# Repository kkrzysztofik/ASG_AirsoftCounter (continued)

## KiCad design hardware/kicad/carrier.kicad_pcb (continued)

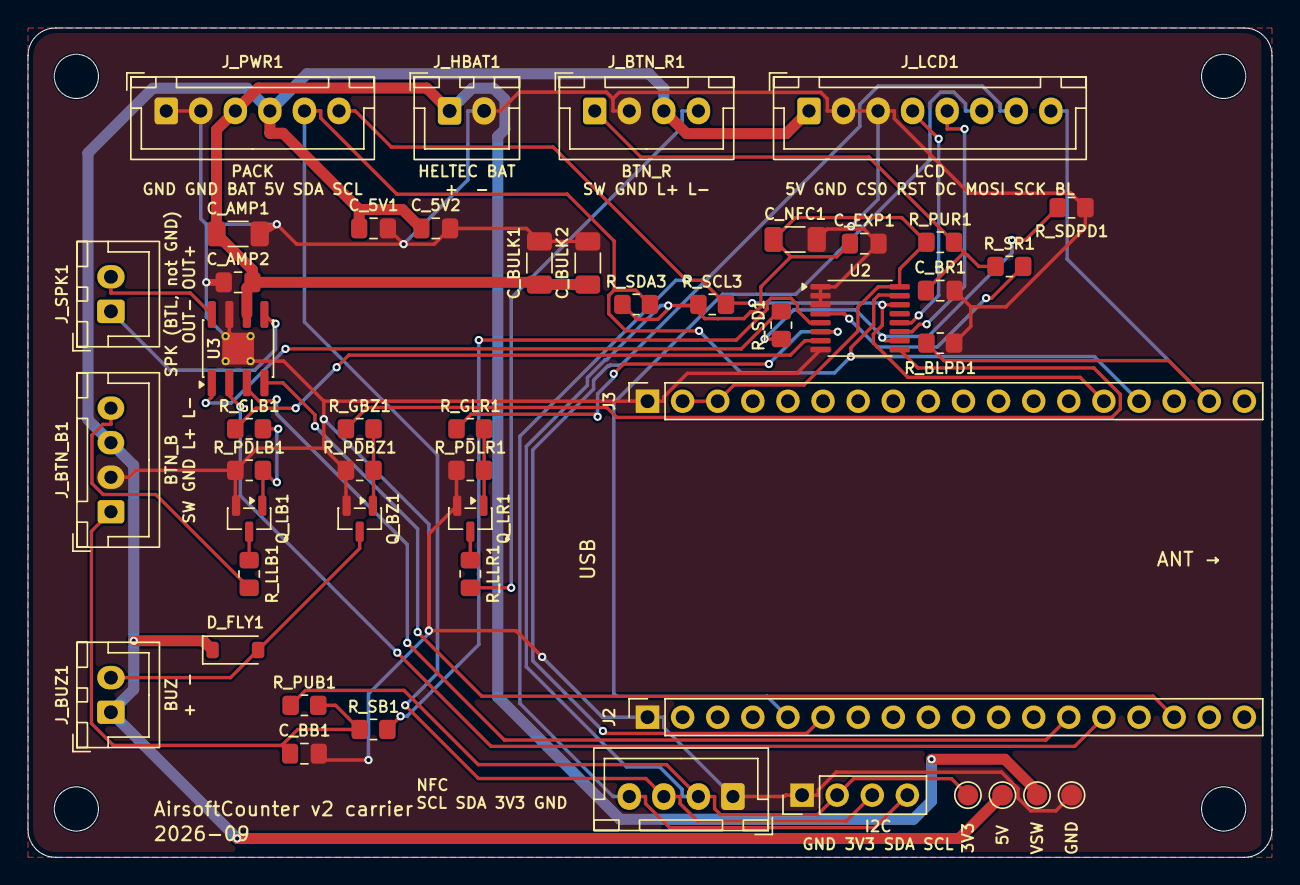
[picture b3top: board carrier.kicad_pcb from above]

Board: 2 copper layers, 90.0 x 60.0 mm, 52 parts (0 on the bottom side), 33 nets.

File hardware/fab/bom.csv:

"Refs","Value","Footprint","Qty"
"C_AMP1,C_NFC1","100uF 6.3V","Capacitor_SMD:C_1206_3216Metric_Pad1.33x1.80mm_HandSolder","2"
"C_AMP2,C_BB1,C_BR1,C_EXP1","100nF","Capacitor_SMD:C_0805_2012Metric_Pad1.18x1.45mm_HandSolder","4"
"C_BULK1,C_BULK2","47uF 10V","Capacitor_SMD:C_1206_3216Metric_Pad1.33x1.80mm_HandSolder","2"
"D_FLY1","1N4148W","Diode_SMD:D_SOD-123","1"
"J2","Heltec_J2","Connector_PinSocket_2.54mm:PinSocket_1x18_P2.54mm_Vertical","1"
"J3","Heltec_J3","Connector_PinSocket_2.54mm:PinSocket_1x18_P2.54mm_Vertical","1"
"J_BTN_B1","BTN_B","Connector_JST:JST_XH_B4B-XH-A_1x04_P2.50mm_Vertical","1"
"J_BTN_R1","BTN_R","Connector_JST:JST_XH_B4B-XH-A_1x04_P2.50mm_Vertical","1"
"J_BUZ1","BUZ","Connector_JST:JST_XH_B2B-XH-A_1x02_P2.50mm_Vertical","1"
"J_HBAT1","HELTEC_BAT","Connector_JST:JST_XH_B2B-XH-A_1x02_P2.50mm_Vertical","1"
"J_LCD1","LCD","Connector_JST:JST_XH_B4B-XH-A_1x04_P2.50mm_Vertical","1"
"J_NFC1","NFC","Connector_JST:JST_XH_B4B-XH-A_1x04_P2.50mm_Vertical","1"
"J_PWR1","PWR","Connector_JST:JST_XH_B6B-XH-A_1x06_P2.50mm_Vertical","1"
"J_SPK1","SPK","Connector_JST:JST_XH_B2B-XH-A_1x02_P2.50mm_Vertical","1"
"Q_BZ1,Q_LB1,Q_LR1,Q_SCL1,Q_SDA1","BSS138","Package_TO_SOT_SMD:SOT-23","5"
"R_GBZ1,R_GLB1,R_GLR1,R_SB1,R_SD1,R_SR1","1k","Resistor_SMD:R_0805_2012Metric_Pad1.20x1.40mm_HandSolder","6"
"R_INT1,R_PDBZ1,R_PDLB1,R_PDLR1,R_PUB1,R_PUR1,R_SDPD1","10k","Resistor_SMD:R_0805_2012Metric_Pad1.20x1.40mm_HandSolder","7"
"R_LLB1,R_LLR1","0R","Resistor_SMD:R_0805_2012Metric_Pad1.20x1.40mm_HandSolder","2"
"R_SCL3,R_SDA3","4k7","Resistor_SMD:R_0805_2012Metric_Pad1.20x1.40mm_HandSolder","2"
"U2","TCA9534PWR","Package_SO:TSSOP-16_4.4x5mm_P0.65mm","1"
"U3","NS4168","Package_SO:HSOP-8-1EP_3.9x4.9mm_P1.27mm_EP2.3x2.3mm_ThermalVias","1"

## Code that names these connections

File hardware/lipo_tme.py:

"""AirsoftCounter LiPo board, hand-build TME variant: iron-only, everything from TME.

Derived from lipo.py by import and edit: STM32L072KZT6 for the C071 (the L072 keeps the
same LQFP-32 and adds crystal-less USB), AP7381-33SA-7 for the HT7533-1 (SOT-23), and a TME
table instead of LCSC (nothing is machine-placed). gen_sch.py / gen_pcb.py read it through
board.py (`make BOARD=lipo_tme ...`). Run this file to self-check (`/usr/bin/python3
lipo_tme.py`).

Source of truth: docs/plans/2026-10-02-tme-hand-build-design.md.
"""
import board
import lipo
import tme

NAME = "lipo_tme"
TITLE = "AirsoftCounter v2 LiPo (hand-build)"

# Footprint tuples shared with the JLC original.
LQFP32, SOT23 = lipo.LQFP32, lipo.SOT23

PARTS = dict(lipo.PARTS)
PARTS["U_MCU"] = ("STM32L072KZT6", "MCU_ST_STM32L0:STM32L072KZTx", LQFP32)
PARTS["U_LDO"] = ("AP7381-33SA-7", "Regulator_Linear:AP7381-33SA-7", SOT23)
PARTS["C_MCU3"] = ("100nF", *lipo.C0805)      # second VDD pin (17)
PARTS["C_VDDA"] = ("1uF", *lipo.C0805)        # VDDA (5); value per the design doc's Parts section
PARTS["TP_BOOT0"] = ("BOOT0", "Connector:TestPoint", lipo.TP)
PARTS["TP_SWCLK"] = ("SWCLK", *lipo.PARTS["TP_SWCLK"][1:])
# TPS563200 for the TPS54302 (TME had none, 2026-10-02): same SOT-23-6 pins, but VFB 0.765 V, 2.2-4.7 uH
# and VIN 17 V max (19 V abs): 3S tops out at 12.6 V. 0.765 x (1 + 22/5.1) = 4.07 V, x (1 + 56/10) = 5.05 V.
for _u, _l in (("U_BA", "L_A"), ("U_BB", "L_B")):
    PARTS[_u] = ("TPS563200DDCR", "Regulator_Switching:TPS563200", lipo.TSOT23_6)
    PARTS[_l] = ("3u3", "Device:L", lipo.LRN6045)
PARTS["R_FBA1"] = ("22k", *lipo.R0805)
PARTS["R_FBB1"] = ("56k", *lipo.R0805)

# AP7381-33SA-7 SOT-23: 1 VI, 2 VO, 3 GND (the HT7533-1 was 1 GND, 2 VIN, 3 VOUT).
LDO_VIN = "U_LDO.1"
TAP_ADC_PIN = {1: "U_MCU.7", 2: "U_MCU.8", 3: "U_MCU.9"}   # PA1-PA3

NETS = {n: [p for p in mem if not p.startswith(("U_MCU.", "U_LDO."))]
        for n, mem in lipo.NETS.items()}
NETS["VIN"] += ["U_LDO.1"]
NETS["+3V3"] += ["U_LDO.2", "U_MCU.1", "U_MCU.17", "U_MCU.5", "C_MCU3.1", "C_VDDA.1"]
NETS["GND"] += ["U_LDO.3", "U_MCU.16", "U_MCU.32", "C_MCU3.2", "C_VDDA.2"]
NETS["NRST"] += ["U_MCU.4"]
NETS["BOOT0"] = ["U_MCU.31", "R_BOOT.1", "TP_BOOT0.1"]       # dedicated BOOT0 pin
NETS["SWCLK"] = ["U_MCU.24", "TP_SWCLK.1"]
NETS["SWDIO"] = ["U_MCU.23", "TP_SWDIO.1"]
NETS["SCL_EXT"] = ["U_MCU.29", "J_PWR1.6"]                   # I2C1, the bootloader port
NETS["SDA_EXT"] = ["U_MCU.30", "J_PWR1.5"]
NETS["UART_TX"] += ["U_MCU.19"]                              # PA9, USART1_TX
NETS["UART_RX"] += ["U_MCU.20"]                              # PA10, USART1_RX
NETS["KILL_DRV"] = ["R_KILL.1", "U_MCU.14"]                  # PB0
for i in (1, 2, 3):
    NETS[f"TAP{i}_ADC"] += [TAP_ADC_PIN[i]]
# Unused L072 pins: PC14/15, PA0/PA4-7, PB1, PA8-12, PA15, PB3-5.
NC_PINS = {f"U_MCU.{p}" for p in (2, 3, 6, 10, 11, 12, 13, 15, 18, 21, 22, 25, 26, 27, 28)}

DNP, NC_PARTS = set(lipo.DNP), set()
# Test pads and the input pigtail are copper only (not bought, not in the BOM export), same as the
# JLC board: gen_sch marks them in_bom=no and gen_pcb must agree or DRC flags a parity mismatch.
NOT_ASSEMBLED = set(lipo.NOT_ASSEMBLED) | {"TP_BOOT0"}
# Not bought at TME: test pads and the input pigtail's pads are copper only.
NOT_TME = {"J_IN1", "TP_SWDIO", "TP_SWCLK", "TP_NRST", "TP_3V3", "TP_GND", "TP_BOOT0", "J_UART1"}
LCSC = {}
_KEYS = {(v, fp) for r, (v, _, fp) in PARTS.items() if r not in NOT_TME and fp != lipo.MH}
TME = tme.from_lcsc(lipo.LCSC, _KEYS)
TME |= {
    ("STM32L072KZT6", LQFP32): "STM32L072KZT6",
    ("AP7381-33SA-7", SOT23): "AP7381-33SA-7",
    ("1uF", lipo.C0805[1]): "CL21B105KAFNNNE",
    ("TPS563200DDCR", lipo.TSOT23_6): "TPS563200DDCR",
    ("3u3", lipo.LRN6045): "SRN6045-3R3Y",            # plain SRN6045, Isat 5 A; fits the TA pads
    ("22k", lipo.R0805[1]): "SMD0805-22K-1%",
    ("56k", lipo.R0805[1]): "SMD0805-56K-1%",
}
MODULES, VARIANTS = {}, {"standard": set()}


def assembled(variant="standard"):
    """Nothing is machine-placed on a hand-build board."""
    return []


# --- layout: reused from lipo by assignment; edited where the parts above need it ------------
W, H, CORNER = lipo.W, lipo.H, lipo.CORNER
NETCLASS_POWER = lipo.NETCLASS_POWER
RAILS = lipo.RAILS
PORT_LIB = lipo.PORT_LIB
NETCLASS_EXPECT = lipo.NETCLASS_EXPECT
DRC_RULES = lipo.DRC_RULES
BOTTOM = lipo.BOTTOM
GND_VIAS = lipo.GND_VIAS
HELTEC_PADS = lipo.HELTEC_PADS
LABELS = lipo.LABELS
TEXTS = list(lipo.TEXTS)
SIZE_MM = lipo.SIZE_MM
NPTH_XY = lipo.NPTH_XY
HIDE_REF = lipo.HIDE_REF + ("TP_BOOT0",)
PLACE = dict(lipo.PLACE)
PLACE |= {
    # L072 VDD/VDDA decoupling in the free strip right of the MCU; TP_BOOT0 joins the test-pad row.
    "C_MCU3": (19.5, 33, 0), "C_VDDA": (24.5, 33, 0),
    "TP_BOOT0": (14.8, 47, 0),
}
REF_AT = dict(lipo.REF_AT)
REF_AT |= {"C_MCU3": (19.5, 31.3, 0), "C_VDDA": (24.5, 34.5, 0)}
_tags = lipo._tags


def _copy_blocks():
    out = []
    for b in lipo.BLOCKS:
        nb = dict(b)
        nb["parts"] = dict(b["parts"])
        if "tags" in b:
            nb["tags"] = {n: list(t) for n, t in b["tags"].items()}
        if "fields" in b:
            nb["fields"] = {r: dict(f) for r, f in b["fields"].items()}
        if "flags" in b:
            nb["flags"] = list(b["flags"])
        if "wired" in b:
            nb["wired"] = set(b["wired"])
        out.append(nb)
    return out


BLOCKS = _copy_blocks()
# MCU block: the L072 adds two supply caps. Its dedicated BOOT0 test pad (TP_BOOT0) is a root part,
# drawn in the bring-up row like lipo's other test pads.
_mcu = next(b for b in BLOCKS if b["title"].startswith("Always-on"))
_mcu["title"] = "Always-on 3V3, STM32L072, SWD pads"
_mcu["parts"] |= {
    "C_MCU3": (30.48, 58.42, 0, None),     # pin 17 VDD
    "C_VDDA": (30.48, 76.2, 0, None),      # pin 5 VDDA
}

# --- Hierarchical schematic: lipo's sheets, root and off-board parts, edited for the L072 -------------
SHEETS = dict(lipo.SHEETS)
SHEETS["bucks"] = ("Buck A 4.07 V (VBAT_SW), buck B 5.05 V (+5V)", lipo.SHEETS["bucks"][1])
SHEETS["mcu"] = ("Always-on 3V3 and STM32L072", lipo.SHEETS["mcu"][1])
# lipo's root, plus the L072's BOOT0 pad at the same 15.24 mm pitch as the other bring-up pads.
ROOT = dict(lipo.ROOT)
ROOT["parts"] = {**lipo.ROOT["parts"], "TP_BOOT0": (50.8, 182.88, 0, None)}
OFFBOARD = dict(lipo.OFFBOARD)


def check_mcu():
    """The L072 pin roles this board relies on."""
    net_of = {p: n for n, mem in NETS.items() for p in mem}
    want = {"U_MCU.1": "+3V3", "U_MCU.17": "+3V3", "U_MCU.5": "+3V3", "U_MCU.16": "GND",
            "U_MCU.32": "GND", "U_MCU.4": "NRST", "U_MCU.31": "BOOT0", "U_MCU.23": "SWDIO",
            "U_MCU.24": "SWCLK", "U_MCU.29": "SCL_EXT", "U_MCU.30": "SDA_EXT",
            "U_LDO.1": "VIN", "U_LDO.2": "+3V3", "U_LDO.3": "GND"}
    for p, n in want.items():
        assert net_of.get(p) == n, f"{p} on {net_of.get(p)}, want {n}"


def check():
    import sys

    this = sys.modules[__name__]
    board.check_structure(this)
    lipo.check_power_path(this)
    check_mcu()
    lipo.check_sheets(this)
    print(f"lipo_tme ok: {len(PARTS)} parts, {len(NETS)} nets")


if __name__ == "__main__":
    check()

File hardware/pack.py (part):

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    "C_SYS": ("10uF", *C0805),
    "C_BAT": ("10uF", *C0805),
    "C_REGN": ("4u7", *C0805),
    # 1206 0R jumpers (2 A rated, <50 mOhm) split the QFN's BAT/SYS pins from the wide rails, so the
    # rails can take the 0.8 mm Power class without crowding the 0.5 mm-pitch pads. Two in parallel
    # for BAT: the 2.048 A charge default (I2C watchdog) crosses them. SYS carries only the load.
    "R_BAT1": ("0R", "Device:R", R1206),
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    "TP_GND": ("GND", "Connector:TestPoint", TP),
    "J_UART1": ("UART", "Connector_Generic:Conn_01x03", HDR3),   # 1 GND, 2 MCU TX, 3 MCU RX; hand-soldered
    # Bring-up test pads on the 3.3 V I2C pair that J_PWR1 carries (SDA_EXT/SCL_EXT, slave 0x30). The
    # rails need none: J_PWR1 pins 3/4 are VBAT_SW and +5V, J_KEY1.1 is SYS, C_MCU1 is 3V3.
    "TP_SDA": ("SDA", "Connector:TestPoint", TP), "TP_SCL": ("SCL", "Connector:TestPoint", TP),
    # --- power out: key switch, 2 A PTC, boost (same parts as carrier.py), 6-pin XH to the carrier ---
    "J_KEY1": ("KEY", "Connector_Generic:Conn_01x02", XH2),
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# PAC1934 (SENSE+, SENSE-) per cell. SENSE+ is also the VBUS input, on the cell side of the shunt,
# so each channel reads its own cell with the switch open.
SENSE_IN = {1: ("11", "12"), 2: ("13", "14"), 3: ("8", "7"), 4: ("10", "9")}
# MCU pin per cell: switch gate drive (PB0/PB1/PB2/PA8) and NTC ADC (PA0..PA3).
SW_PIN = {1: "15", 2: "16", 3: "17", 4: "18"}
NTC_PIN = {1: "7", 2: "8", 3: "9", 4: "10"}

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    "NRST": ["U_MCU.6", "C_NRST.1", "SW_RST.1", "TP_NRST.1"],
    "BOOT0": ["U_MCU.25", "R_BOOT.1", "SW_BOOT.1", "TP_SWCLK.1"],
    "SWDIO": ["U_MCU.24", "TP_SWDIO.1"],
    "UART_TX": ["U_MCU.19", "J_UART1.2"],     # PA9, USART1_TX
    "UART_RX": ["U_MCU.21", "J_UART1.3"],     # PA10, USART1_RX
    "LED_MCU_DRV": ["U_MCU.26", "R_LED_MCU.1"],
    "LED_MCU_A": ["R_LED_MCU.2", "LED_MCU.2"],
    # external I2C (slave 0x30) to the carrier: no pull-ups here
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
# --- layout (read by gen_sch.py / gen_pcb.py / check_gerbers.py) --------------------------------
# Rails carry power_in pins, so ERC needs a driver on each: +3V3 has the LDO's power_out, the others
# take a PWR_FLAG (their sources are all passive). +5V and SYS have no power_in pin, so they stay
# ordinary labelled nets.
# Nets that get the wider Power class. "SW*" would also catch the MCU's SW*_DRV gate signals (uA),
# which must reach the LQFP32's 0.8 mm-pitch pads, so only the two switching nodes are listed.
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
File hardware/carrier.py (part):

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    PARTS[f"R_S{t}1"] = ("1k", *R0805)
    PARTS[f"C_B{t}1"] = ("100nF", *C0805)
PARTS["C_EXP1"] = ("100nF", *C0805)  # U2 decoupling
# LCD backlight PWM (GPIO6) pull-down: dark until firmware drives it. U2's INT is unused (buttons polled).
PARTS["R_BLPD1"] = ("10k", *R0805)
PARTS["C_AMP2"] = ("1uF", *C0805)  # U3 VDD decoupling (next to C_AMP1); NS4168 datasheet 10.4: 100 uF || 1 uF
# +5V arrives over the pack cable from the MT3608 boost (its 2x 22 uF stay on the pack board): a local
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    "VBAT_SW": ["J_HBAT1.1", "C_BULK1.1", "C_BULK2.1", "U3.6", "C_AMP1.1", "C_AMP2.1", "J_PWR1.3", "TP_VSW.1"],
    "+5V": ["J_PWR1.4", "J_LCD1.1", "TP_5V.1", "J_BTN_R1.3", "J_BTN_B1.3", "J_BUZ1.1",
            "D_FLY1.1", "C_5V1.1", "C_5V2.1"],
    # Display on SPI3 (GPIO matrix): clock and data on the ex-UART0 pins, backlight PWM (LEDC) on GPIO6,
    # DC and reset on the expander (DC only toggles between command and data phases)
    "LCD_SCK": ["J2.6", "J_LCD1.7"],            # GPIO43 (ROM boot log toggles it: harmless, CS-less reset follows)
    "LCD_MOSI": ["J2.5", "J_LCD1.6"],           # GPIO44
    "LCD_BL": ["J3.17", "R_BLPD1.1", "J_LCD1.8"],  # GPIO6
    "LCD_DC": ["U2.11", "J_LCD1.5"],            # expander P6
    "LCD_RST": ["U2.12", "J_LCD1.4"],           # expander P7
    # I2C
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    "J2.13": 47, "J2.14": 48, "J2.15": 26, "J2.16": 21, "J2.17": 20, "J2.18": 19,
}
# Used internally on V4-R2 or V4-R8 (FEM, GNSS, PSRAM, strapping, USB, LED/Vext, VBAT), or RST.
# GPIO3 is a strapping pin (JTAG source select), but only if the STRAP_JTAG_SEL
# efuse is burned. With default efuses it is safe for SCL, so it is not forbidden.
FORBIDDEN_GPIO = {0, 1, 2, 5, 7, 19, 20, 26, 33, 34, 35, 36, 37, 38, 39, 40, 41, 42, 45, 46, None}
EXPECTED_GPIO = {"SCL_3V3": 3, "SDA_3V3": 4, "LCD_BL": 6,
                 "I2S_BCLK": 47, "I2S_LRCLK": 48, "I2S_DIN": 21, "LCD_SCK": 43, "LCD_MOSI": 44}
HEADER_POWER = {"J2.1": "GND", "J3.1": "GND", "J3.2": "+3V3", "J3.3": "+3V3"}
HEADER_NC = {"J2.2", "J2.3", "J2.4"}  # 5V charger input, Vext x2: must stay unconnected
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# symbol keeps ERC's library check (lib_symbol_issues) clean with no ignore.
PORT_LIB = {"GND": "power:GND", "+3V3": "power:+3V3", "+5V": "power:+5V", "VBAT_SW": "power:+BATT"}
NC_PARTS = {"J2", "J3"}  # every unconnected pin gets a no-connect flag
NC_PINS = {"U2.13"}  # TCA9534 INT: buttons are polled, GPIO6 went to the LCD backlight


# --- Layout: blocks of hand-placed parts ---
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
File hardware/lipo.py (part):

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    "NRST": ["U_MCU.6", "C_NRST.1", "TP_NRST.1"],
    "BOOT0": ["U_MCU.25", "R_BOOT.1", "TP_SWCLK.1"],
    "SWDIO": ["U_MCU.24", "TP_SWDIO.1"],
    "UART_TX": ["U_MCU.19", "J_UART1.2"],     # PA9, USART1_TX
    "UART_RX": ["U_MCU.21", "J_UART1.3"],     # PA10, USART1_RX
    "SDA_EXT": ["U_MCU.13", "J_PWR1.5"],     # slave 0x30, pull-ups on the carrier
    "SCL_EXT": ["U_MCU.14", "J_PWR1.6"],
    "GND": ["J_IN1.2", "R_REV1.2", "D_TVS1.2", "C_VIN1.2", "C_VIN2.2", "C_VIN3.2", "C_VIN4.2",
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            "J_BAL1.1", "R_TB1.2", "R_TB2.2", "R_TB3.2", "C_TAP1.2", "C_TAP2.2", "C_TAP3.2",
            "J_PWR1.1", "J_PWR1.2"],
}
# Balance taps: plug pin i+1 -> top resistor -> ADC node (bottom resistor + 100 nF) -> PA0..PA2.
NETS["BAL1"] = ["J_BAL1.2", "R_TT1.1"]
NETS["BAL2"] = ["J_BAL1.3", "R_TT2.1"]
NETS["BAL3"] = ["J_BAL1.4", "R_TT3.1"]
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BLOCKS = [
    {"title": "LiPo input: fuse, reverse FET, TVS", "at": (12.7, 12.7), "size": (127.0, 88.9),
     # VIN is made here by a passive FET, so its one PWR_FLAG stays on this sheet, beside the input.
     # LIPO_RAW leaves for J_IN1 on the root: a tag in the free space J_IN1 leaves behind (a label on
     # F_IN1's own top pin would run into the block title above it).
     "tags": {"LIPO_RAW": [(12.7, 21.59, "L")]},
     "flags": [("VIN", 12.7, 76.2)],
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
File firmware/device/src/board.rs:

//! Heltec WiFi LoRa 32 V4 (no display) + AirsoftCounter carrier. See design doc parts 1 and 6.
//! The only file that names GPIOs: the numbers below document the map, `Board::new` hands out the
//! matching typed pins by role.

use esp_hal::gpio::AnyPin;
use esp_hal::peripherals::{FROM_CPU_INTR0, Peripherals, TIMG0};

pub const I2C_SDA: u8 = 4;
pub const I2C_SCL: u8 = 3;
pub const EXP_INT: u8 = 6; // TCA9534 INT, active low, 10k pull-up on the carrier
pub const I2S_BCLK: u8 = 47;
pub const I2S_LRCLK: u8 = 48;
pub const I2S_DIN: u8 = 21;
pub const VBAT_ADC: u8 = 1;
// GPIO44 (U0RXD) and GPIO43 (U0TXD) are spare and unconnected on this carrier revision.

/// TCA9534 expander (I2C 0x20) pin map.
pub mod exp {
    pub const ADDR: u8 = 0x20;
    pub const BTN_RED: u8 = 0; // input, active low
    pub const BTN_BLUE: u8 = 1; // input, active low
    pub const LED_RED: u8 = 2;
    pub const LED_BLUE: u8 = 3;
    pub const BUZZER: u8 = 4;
    pub const AMP_SD: u8 = 5; // high = amp on (left channel), low = shutdown
    // P6, P7 unconnected: configure as outputs driven low.
}
#[cfg(feature = "v4-r2")]
pub const ONBOARD_LED: u8 = 35;
#[cfg(feature = "v4-r8")]
pub const ONBOARD_LED: u8 = 46;
#[cfg(feature = "v4-r2")]
pub const VEXT: u8 = 36; // active low
#[cfg(feature = "v4-r8")]
pub const VEXT: u8 = 40;
#[cfg(feature = "v4-r2")]
pub const ADC_CTRL: Option<u8> = Some(37);
#[cfg(feature = "v4-r8")]
pub const ADC_CTRL: Option<u8> = None;

/// Peripherals split by role. Later tasks add fields here (I2C, I2S, ADC, ...).
pub struct Board {
    pub onboard_led: AnyPin<'static>,
    /// For the esp-rtos scheduler.
    pub timg0: TIMG0<'static>,
    pub sw_int0: FROM_CPU_INTR0<'static>,
}

impl Board {
    pub fn new(p: Peripherals) -> Self {
        #[cfg(feature = "v4-r2")]
        let onboard_led = p.GPIO35.into();
        #[cfg(feature = "v4-r8")]
        let onboard_led = p.GPIO46.into();
        Self { onboard_led, timg0: p.TIMG0, sw_int0: p.FROM_CPU_INTR0 }
    }
}

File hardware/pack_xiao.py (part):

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
# XIAO pins (symbol = footprint numbers): 1-11 D0..D10, 12 3V3, 13 GND, 14 5V (VBUS),
# 15 MTDI, 16 MTDO (GPIO40), 17 EN, 18 GND, 19 MTMS, 20 MTCK (GPIO39), 21/22 USB, 23 BAT+, 24 GND, 25 PAD.
MCU = {1: "NTC1", 2: "NTC2", 3: "NTC3", 4: "NTC4",       # D0..D3 = GPIO1..4, ADC1
       5: "SDA_EXT", 6: "SCL_EXT",                        # D4/D5, I2C0 slave 0x30
       7: "SCL_INT",                                      # D6 = U0TXD: boot chatter, no START with SDA high
       8: "SW1_DRV", 9: "SW2_DRV", 10: "SW3_DRV", 11: "SW4_DRV",
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
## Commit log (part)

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2018-11-26 Initial commit. AirsoftCoint mode done.
2019-01-22 License added
2019-01-22 Readme
2019-01-22 Readme updated
